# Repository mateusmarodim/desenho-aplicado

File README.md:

# desenho-aplicado
Projeto Final de Desenho Aplicado

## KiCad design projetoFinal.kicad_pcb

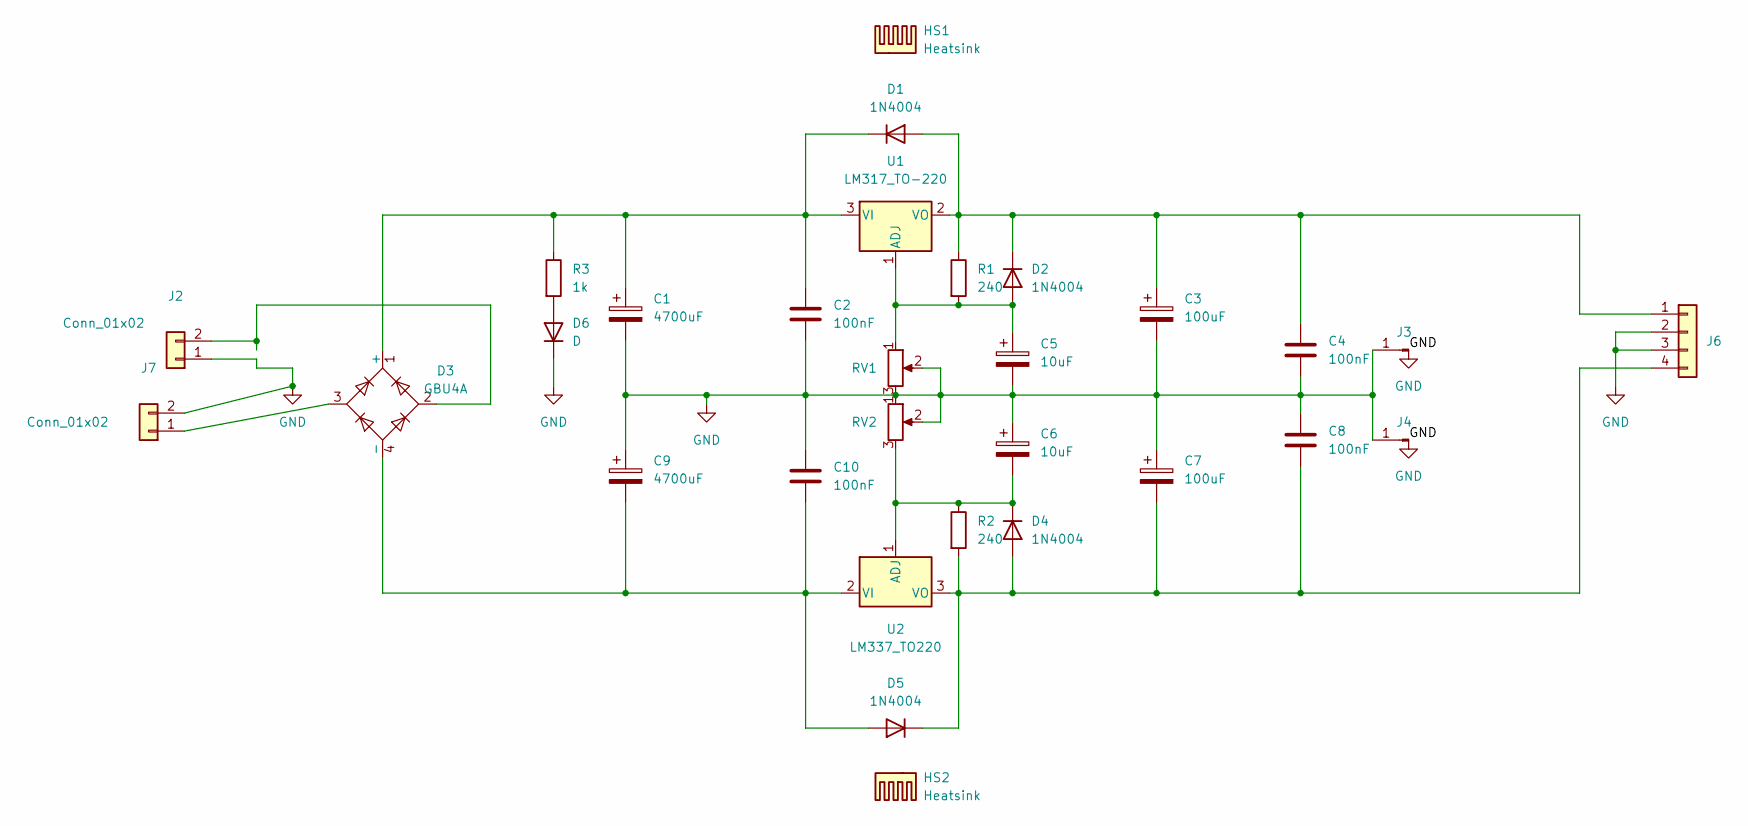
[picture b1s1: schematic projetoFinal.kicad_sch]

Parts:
C1, C9: 4700uF; CP_Radial_D12.5mm_P5.00mm
C2, C4, C8, C10: 100nF; C_Disc_D3.0mm_W2.0mm_P2.50mm
C3, C7: 100uF; CP_Radial_D7.5mm_P2.50mm
C5, C6: 10uF; CP_Radial_D5.0mm_P2.50mm
D1, D2, D4, D5: 1N4004; D_5W_P10.16mm_Horizontal
D3: GBU4A; Diode_Bridge_Vishay_GBU
D6: D; LED_D5.0mm
HS1, HS2: Heatsink; Heatsink_Stonecold_HS-132_32x14mm_2xFixation1.5mm
J2, J7: Conn_01x02; TerminalBlock_Phoenix_MKDS-1,5-2_1x02_P5.00mm_Horizontal
J3, J4: Conn_01x01_Male; Banana_Jack_1Pin
J6: Conn_01x04; PinHeader_1x04_P2.54mm_Vertical
R1, R2: 240; R_Axial_DIN0207_L6.3mm_D2.5mm_P10.16mm_Horizontal
R3: 1k; R_Axial_DIN0204_L3.6mm_D1.6mm_P7.62mm_Horizontal
RV1, RV2: R_Potentiometer; Potentiometer_Piher_T-16L_Single_Vertical_Hole
U1: LM317_TO-220; TO-220-3_Vertical
U2: LM337_TO220; TO-220-3_Vertical

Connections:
GND: C1.2, C2.2, C3.2, C4.2, C5.2, C6.1, C7.1, C8.1, C9.1, C10.1, D6.1 (K), J2.1, J3.1, J4.1, J6.2, J6.3, J7.2, RV1.2, RV1.3, RV2.1, RV2.2
unnamed: C1.1, C2.1, D1.1 (K), D3.1 (+), R3.1, U1.3 (VI)
unnamed 2: C3.1, C4.1, D1.2 (A), D2.1 (K), J6.1, R1.1, U1.2 (VO); also elsewhere on the board
unnamed: C5.1, D2.2 (A), R1.2, RV1.1, U1.1 (ADJ)
unnamed: C6.2, D4.1 (K), R2.1, RV2.3, U2.1 (ADJ)
unnamed 5: C7.2, C8.2, D4.2 (A), D5.1 (K), J6.4, R2.2, U2.3 (VO); also elsewhere on the board
unnamed: C9.2, C10.2, D3.4 (-), D5.2 (A), U2.2 (VI)
unnamed: D3.2, J2.2
unnamed: D3.3, J7.1
unnamed: D6.2 (A), R3.2

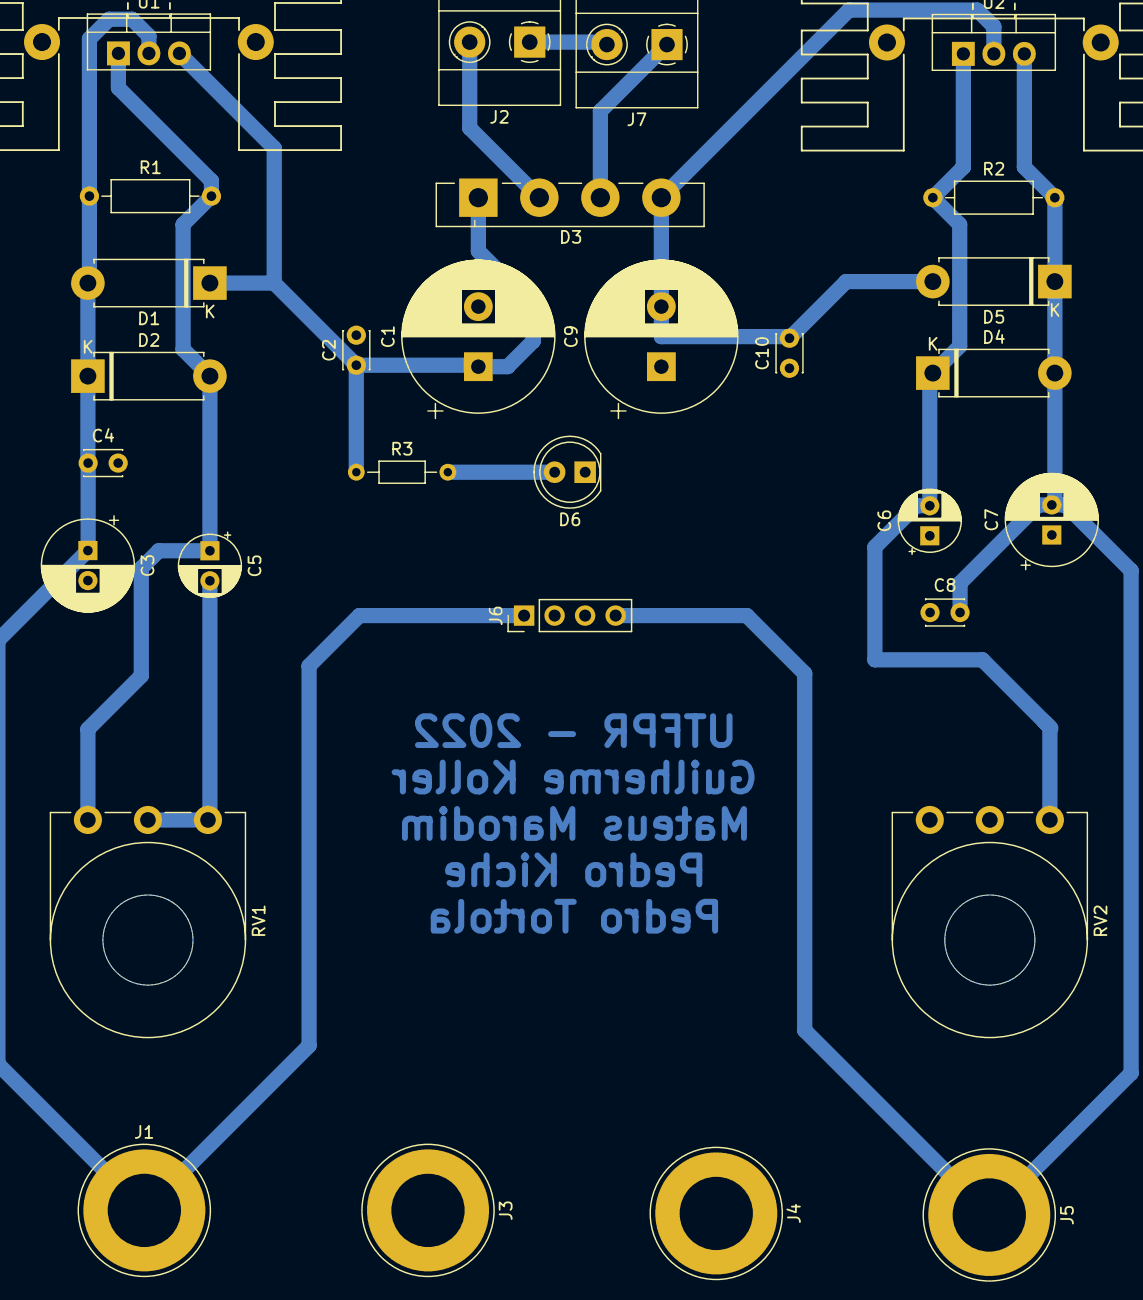
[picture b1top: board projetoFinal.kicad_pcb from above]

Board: 2 copper layers, 32 parts (0 on the bottom side), 10 nets.

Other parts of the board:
J1, J5: Conn_01x01_Male; Banana_Jack_1Pin

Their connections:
unnamed 2: J1.1; also elsewhere on the board
unnamed 5: J5.1; also elsewhere on the board

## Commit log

2022-05-27 coloquei uns footprint e deve estar tudo errado
2022-05-31 footprints quase certos
2022-06-01 roteamento feito
2022-06-01 novo roteamento da placa
2022-06-01 layout final
2022-06-02 fonte dos nomes aumentada
2022-06-09 correção final na placa
